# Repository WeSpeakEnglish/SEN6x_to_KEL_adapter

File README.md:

# SEN6x_to_KEL_adapter

Adapter board that connects a **Sensirion SEN6x** environmental sensor (SEN63C, SEN65, SEN66, SEN68…) to a **KEL I²C interface**. The sensor is normally powered from the KEL connector, and it can also run from an **external USB-C power supply**. When USB-C power is present, the board switches over to it automatically.

Full schematic: [schematic.pdf](schematic.pdf)

## Features

- Passes I²C (SDA/SCL) straight from the KEL connector to the SEN6x sensor connector
- On-board 3.3 V LDO regulator (NCP1117-3.3) supplies the sensor
- Two power sources:
  - **KEL 5 V** (default)
  - **USB-C 5 V** (external, takes priority when plugged in)
- Automatic power-source selection with no jumpers needed
- I²C pull-ups to 3.3 V on board
- USB-C port is power-only, with CC termination so any standard USB-C charger delivers 5 V

## Connectors

### J3 – KEL I²C (Conn_01x05)

| Pin | Signal | Note |
|-----|--------|------|
| 1 | GND | |
| 2 | SDA | I²C data |
| 3 | SCL | I²C clock |
| 4 | NC | not connected |
| 5 | 5V | supply from KEL |

### J2 – SEN6x sensor (Conn_01x06)

| Pin | Signal |
|-----|--------|
| 1 | +3.3 V |
| 2 | GND |
| 3 | SDA |
| 4 | SCL |
| 5 | GND |
| 6 | +3.3 V |

The pinout matches the Sensirion SEN6x interface cable. The SEN6x default I²C address is `0x6B`.

### J1 – USB-C (power only)

This port is used only for external 5 V power and carries no USB data.

## How it works

### Power path

```
KEL 5V ──► Q2 (switch) ──┐
                         ├──► U1 NCP1117-3.3 ──► +3.3 V ──► SEN6x
USB VBUS ──► D1 (B230) ──┘
```

- **KEL supply only:** Q2 (BC817) is biased on through R4 (510 Ω) and passes the KEL 5 V to the LDO input.
- **USB-C connected:** VBUS feeds the LDO input through Schottky diode D1 (B230). At the same time, the R1/R2 divider (2 × 5.1 kΩ) turns on Q1 (BC817). Q1 pulls the base of Q2 low through R3 (510 Ω) and switches Q2 off. The sensor then runs from USB-C power and draws no current from the KEL 5 V rail.
- D1 blocks reverse current into the USB-C port while the board runs from KEL power.
- R7/R8 (5.1 kΩ) on CC1/CC2 are the standard USB-C sink (Rd) resistors. They make a USB-C source switch VBUS on.
- C1 (0.1 µF) and C2 (1 µF) are the input and output capacitors of the LDO.

### I²C

- SDA and SCL are pulled up to +3.3 V. Each line has two 5.1 kΩ footprints: R6/R9 on SDA and R5/R10 on SCL.
  - Fit one resistor per line for 5.1 kΩ.
  - Fit both resistors per line for about 2.55 kΩ, which suits longer cables or faster clocks.
- Bus levels are 3.3 V, so the KEL side must accept 3.3 V I²C logic.

## Bill of materials

| Ref | Value | Description |
|-----|-------|-------------|
| U1 | NCP1117-3.3 | 3.3 V LDO regulator, SOT-223 |
| Q1, Q2 | BC817 | NPN transistor, SOT-23 |
| D1 | B230 | Schottky diode |
| C1 | 0.1 µF | LDO input capacitor |
| C2 | 1 µF | LDO output capacitor |
| R1, R2 | 5.1 kΩ | VBUS sense divider |
| R3, R4 | 510 Ω | Q2 bias |
| R5, R6, R9, R10 | 5.1 kΩ | I²C pull-ups |
| R7, R8 | 5.1 kΩ | USB-C CC pull-downs (Rd) |
| J1 | USB-C receptacle | power-only, 6-pin |
| J2 | 6-pin connector | SEN6x sensor |
| J3 | 5-pin header | KEL I²C |

## Repository contents

| Path | Content |
|------|---------|
| `adapter/` | KiCad project (schematic and PCB) |
| `schematic.pdf` | schematic as a PDF |
| `PCB.png` | 3D render of the board |

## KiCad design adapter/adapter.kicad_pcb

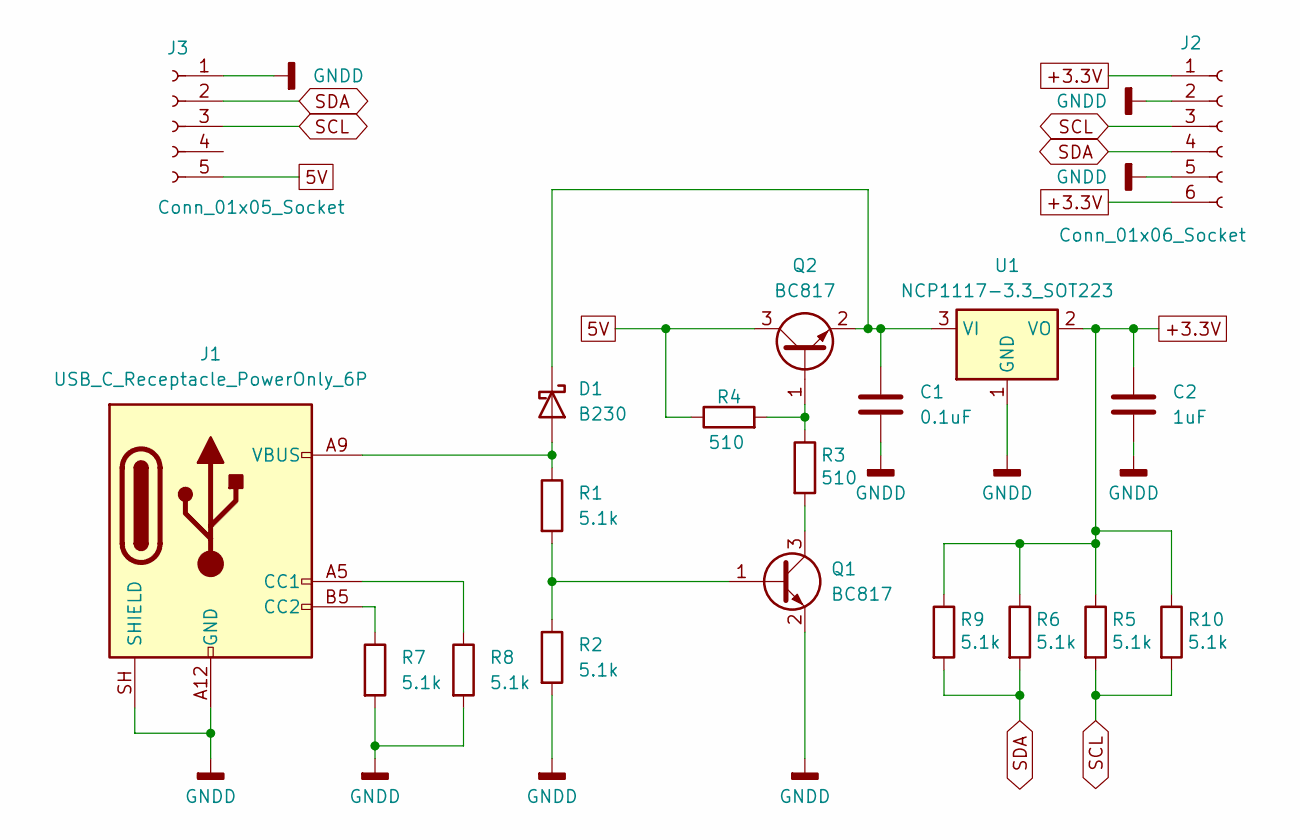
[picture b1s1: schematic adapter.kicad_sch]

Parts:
C1: 0.1uF; C_0805_2012Metric_Pad1.18x1.45mm_HandSolder
C2: 1uF; C_0805_2012Metric_Pad1.18x1.45mm_HandSolder
D1: B230; D_SMB
J1: USB_C_Receptacle_PowerOnly_6P; USB_C_Receptacle_GCT_USB4125-xx-x_6P_TopMnt_Horizontal
J2: Conn_01x06_Socket; JST_GH_SM06B-GHS-TB_1x06-1MP_P1.25mm_Horizontal
J3: Conn_01x05_Socket; PinHeader_1x05_P2.54mm_Horizontal
Q1, Q2: BC817; SOT-23
R1, R2, R5, R6, R7, R8, R9, R10: 5.1k; R_0805_2012Metric_Pad1.20x1.40mm_HandSolder
R3, R4: 510; R_0805_2012Metric_Pad1.20x1.40mm_HandSolder
U1: NCP1117-3.3_SOT223; SOT-223-3_TabPin2

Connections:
5V: J3.5, Q2.3 (C), R4.1
+3.3V: C2.1, J2.1, J2.6, R5.1, R6.1, R9.1, R10.1, U1.2 (VO)
GNDD: C1.2, C2.2, J1.A12 (GND), J1.B12 (GND), J1.SH (SHIELD), J2.2, J2.5, J3.1, Q1.2 (E), R2.2, R7.2, R8.2, U1.1 (GND)
unnamed: D1.2 (A), J1.A9 (VBUS), J1.B9 (VBUS), R1.1
unnamed: C1.1, D1.1 (K), Q2.2 (E), U1.3 (VI)
unnamed: J1.A5 (CC1), R8.1
unnamed: J1.B5 (CC2), R7.1
unnamed: Q1.1 (B), R1.2, R2.1
unnamed: Q1.3 (C), R3.2
unnamed: Q2.1 (B), R3.1, R4.2
SCL: J2.3, J3.3, R5.2, R10.2
SDA: J2.4, J3.2, R6.2, R9.2

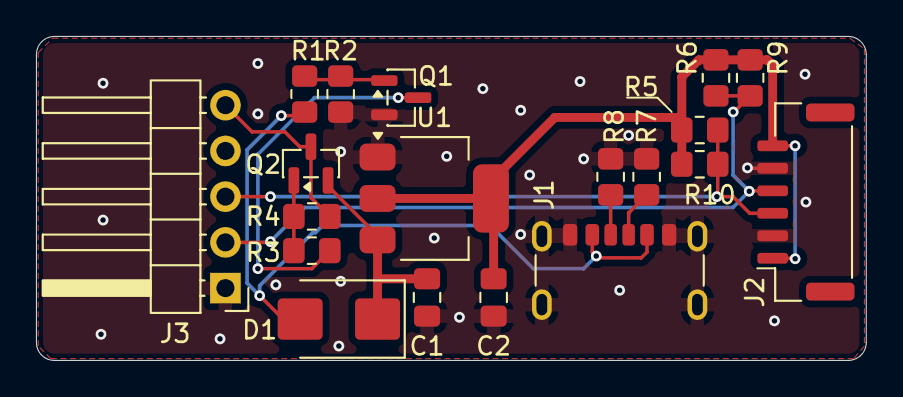
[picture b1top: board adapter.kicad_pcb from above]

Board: 2 copper layers, 46.1 x 18.0 mm, 19 parts (0 on the bottom side), 12 nets.
